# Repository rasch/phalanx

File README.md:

# Phalanx

![The Phalanx Keyboard, Version 0.1.0][image]

The [Phalanx] is a <kbd>4</kbd> <kbd>×</kbd> <kbd>3</kbd> <kbd>+</kbd> <kbd>2</kbd>,
*ortholinear*, *staggered*, *split* keyboard.

- Keyboard Maintainer: [rasch](https://github.com/rasch/phalanx)
- Hardware Supported: Phalanx 0.1.0 (stm32f072)
- Hardware Availability: [phalanx]

## Getting Board

Check out [the Phalanx releases page][releases] for the required files to get
PCBs manufactured (`plot.zip`) and/or assembled (`bom.csv` and `cpl.csv`). For
those with soldering abilities, an interactive BOM/CPL HTML file (`ibom.html`)
is provided to aid with self-assembly.

During development, it may be preferable (faster) to run rule checks and test
builds locally. There is a `run` shell script in the root of this repository
that is used by the CI/CD for building releases. This script can be run
directly (`./run pcb`), but it requires the `kicad-cli` 8.0+ release to be
installed. Instead, if `podman` is available, it is recommended to use the
`build` script. This script just runs the `./run` script in the
`kicad/kicad:8.0` container. The build files and reports (ERC/DRC) are placed in
the `dist` directory.

![The Phalanx Keyboard, Version 0.1.0][image-pcb]

In addition to the parts listed in the BOM, the following will be needed for a
complete keyboard:

- 28 x Kailh Low Profile Choc Switches (PG1350)
- 28 x 1u Choc Keycaps (such as MBK, I prefer the convex keys for the thumbs)
- USB-C cable to connect to device
- RJ45 Ethernet Cable to connect keyboard halves (the monoprice micro slimrun
  patch cable works well, I've used the 6 inch cable)
- Some rubber feet or neoprene adhesive rubber pads to prevent the board from
  sliding all over the place

## Firmware Installation

Download the firmware, `phalanx_default.bin`, from [the Phalanx releases
page][releases]. To flash the keyboard, press the reset button on the PCB to
enter bootloader mode, then run:

```sh
dfu-util -a 0 -d 0483:DF11 -s 0x8000000:leave -D phalanx_default.bin
```

For details on compiling the firmware, please see the [Github Actions
workflow][build].

## Keymap

The base alpha layer is based on the [Engram] layout.

```txt
  B  Y  O  U       L  D  W  V
  C  I  E  A       H  T  S  N
  G  X  J  K       R  M  F  P
            ␣    ⌫
```

[QMK] features such as `Mod-Tap`, `Layers`, `Combos` and `Tap Dance` are
utilized to maximize Phalanx's features with only 27% of the keys from a
standard keyboard. Please visit the [Phalanx website][phalanx] for details of
the layout.

## License

[Solderpad Hardware License v2.1](LICENSE)

[phalanx]: https://www.rasch.co/phalanx
[releases]: https://github.com/rasch/phalanx/releases/
[image]: https://i.imgur.com/y4TYriW.jpg
[image-pcb]: https://i.imgur.com/gtF0UkI.png
[build]: https://github.com/rasch/phalanx/blob/main/.github/workflows/fw.yml
[engram]: https://engram.dev/
[qmk]: https://docs.qmk.fm/#/
[//]: https://en.wikipedia.org/wiki/Phalanx_bone

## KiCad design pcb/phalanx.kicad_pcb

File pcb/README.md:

# Phalanx PCB

![The Phalanx PCB, Version 0.1.0][pcb image]

## Getting Board

Check out [the Phalanx releases page][releases] for the required files to get
PCBs manufactured (`plot.zip`) and/or assembled (`bom.csv` and `cpl.csv`). For
those with soldering abilities, an interactive BOM/CPL HTML file (`ibom.html`)
is provided to aid with self-assembly.

## Build Locally

During development, it may be preferable (faster) to run rule checks and test
builds locally. There is a `run` shell script in the root of this repository
that is used by the CI/CD for building releases. This script can be run
directly (`./run build`), but it requires the `kicad-cli` nightly release to be
installed. Instead, if `podman` is available, it is recommended to use the
`build-pcb` script. This script just runs the `./run` script in the
`kicad/kicad:nightly` container. The build files and reports (ERC/DRC) are
placed in the `dist` directory.

[pcb image]: https://cdn.jsdelivr.net/gh/rasch/phalanx@assets/phalanx-fpcb.webp
[releases]: https://github.com/rasch/phalanx/releases/

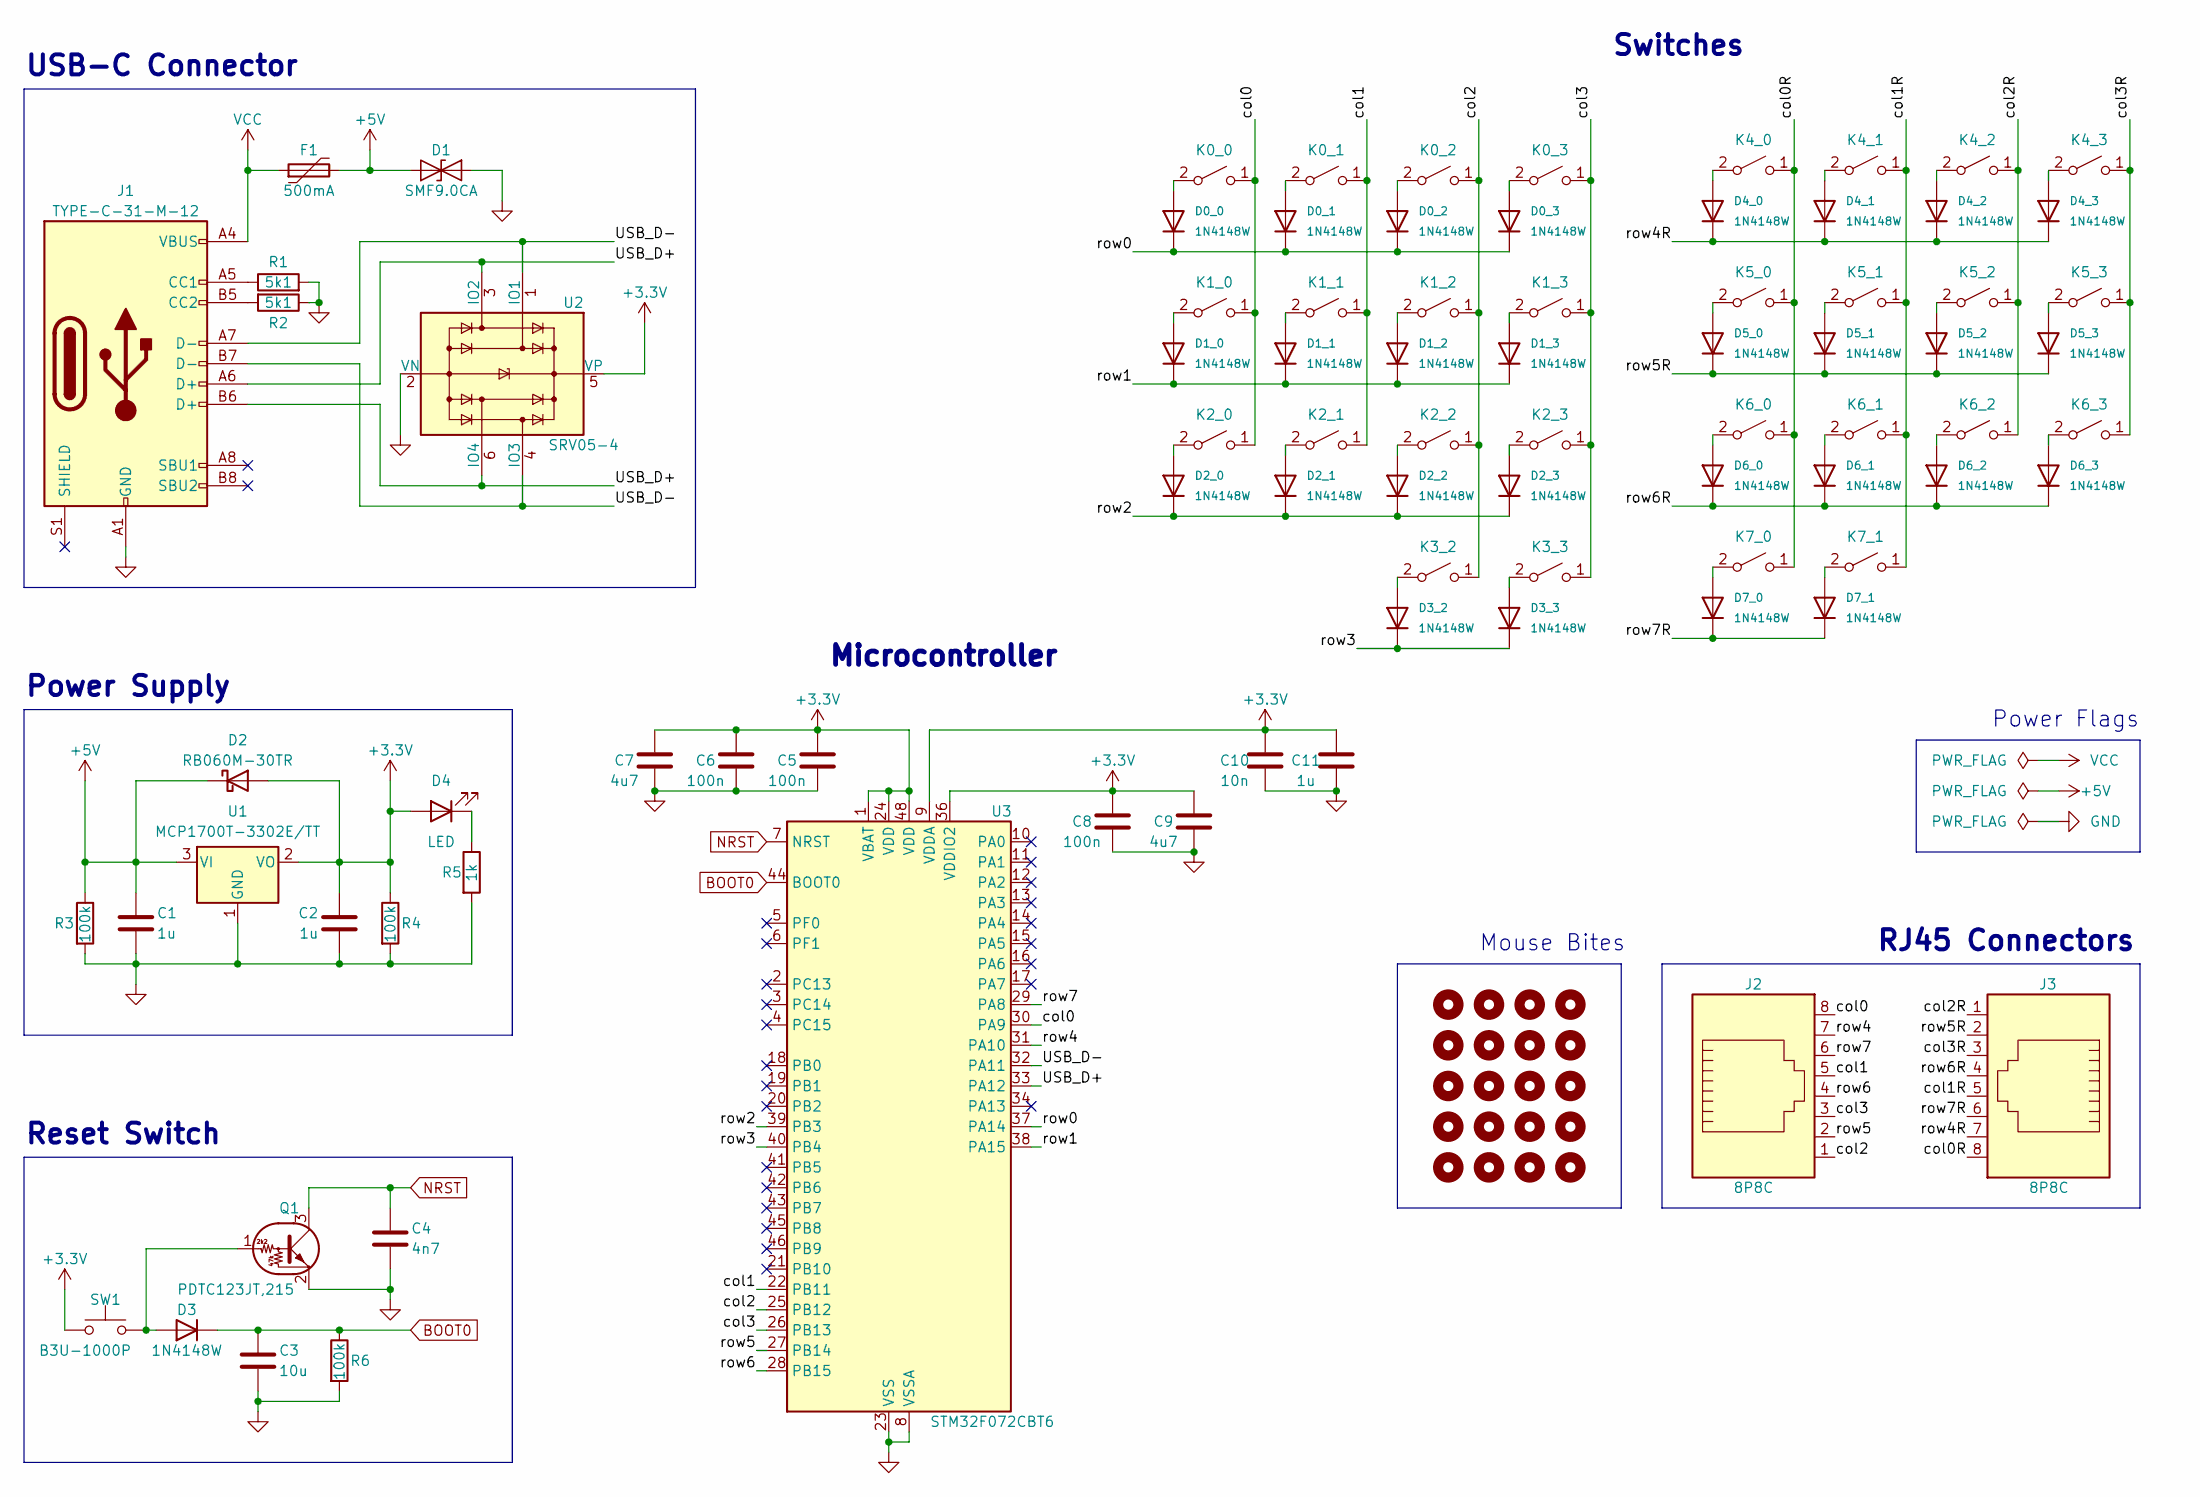
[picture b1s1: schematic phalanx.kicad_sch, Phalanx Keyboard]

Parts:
C1, C2, C11: 1u; C_0805_2012Metric; Part Name Capacitor; LCSC Part C28323
C3: 10u; C_0805_2012Metric; Part Name Capacitor; LCSC Part C17024
C4: 4n7; C_0805_2012Metric; Part Name Capacitor; LCSC Part C717014
C5, C6, C8: 100n; C_0805_2012Metric; Part Name Capacitor; LCSC Part C49678
C7, C9: 4u7; C_0805_2012Metric; Part Name Capacitor; LCSC Part C87998
C10: 10n; C_0805_2012Metric; Part Name Capacitor; LCSC Part C1710
D0_0, D0_1, D0_2, D0_3, D1_0, D1_1, D1_2, D1_3, D2_0, D2_1, D2_2, D2_3, D3, D3_2, D3_3, D4_0, D4_1, D4_2, D4_3, D5_0, D5_1, D5_2, D5_3, D6_0, D6_1, D6_2, D6_3, D7_0, D7_1: 1N4148W; D_SOD-123; Part Name Diode; LCSC Part C81598
D1: SMF9.0CA; D_SOD-123; Part Name Bidirectional Diode; LCSC Part C435473
D2: RB060M-30TR; D_SOD-123; Part Name Schottky Barrier Diodes; LCSC Part C559324
D4: LED; LED_0603_1608Metric; Part Name Red LED; LCSC Part C84263
F1: 500mA; Fuse_1206_3216Metric; Part Name Polyfuse; LCSC Part C151162
H1, H2, H3, H4, H5, H6, H7, H8, H9, H10, H11, H12, H13, H14, H15, H16, H17, H18, H19, H20: MountingHole; MountingHole_0.5mm
J1: TYPE-C-31-M-12; USB_C_Receptacle_HRO_TYPE-C-31-M-12; Part Name USB C; LCSC Part C165948
J2, J3: 8P8C; RJ45; Part Name RJ45 Receptacle; LCSC Part C2902700
K0_0, K0_1, K0_2, K0_3, K1_0, K1_1, K1_2, K1_3, K2_0, K2_1, K2_2, K2_3, K3_2, K3_3, K4_0, K4_1, K4_2, K4_3, K5_0, K5_1, K5_2, K5_3, K6_0, K6_1, K6_2, K6_3, K7_0, K7_1: SW_KEY; Choc_PG1350_Choc_Spacing
Q1: PDTC123JT,215; SOT-23; Part Name NPN Transistor; LCSC Part C406040
R1, R2: 5k1; R_0805_2012Metric; Part Name Resistor; LCSC Part C27834
R3, R4, R6: 100k; R_0805_2012Metric; Part Name Resistor; LCSC Part C149504
R5: 1k; R_0805_2012Metric; Part Name Resistor; LCSC Part C17513
SW1: B3U-1000P; SW_SPST_B3U-1000P; Part Name Reset Button; LCSC Part C231329
U1: MCP1700T-3302E/TT; SOT-23; Part Name Dropout Regulator; LCSC Part C39051
U2: SRV05-4; SOT-23-6; Part Name TVS Diode Array; LCSC Part C558418
U3: STM32F072CBT6; LQFP-48_7x7mm_P0.5mm; Part Name MCU; LCSC Part C81720

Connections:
+3.3V: C2.1, C5.1, C6.2, C7.1, C8.2, C9.2, C10.2, C11.2, D2.2 (A), D4.2 (A), R4.1, SW1.1, U1.2 (VO), U2.5 (VP), U3.1 (VBAT), U3.9 (VDDA), U3.24 (VDD), U3.36 (VDDIO2), U3.48 (VDD)
+5V: C1.1, D1.1 (A1), D2.1 (K), F1.2, R3.1, U1.3 (VI)
/USB_D+: J1.A6 (D+), J1.B6 (D+), U2.3 (IO2), U2.6 (IO4), U3.33 (PA12)
/USB_D-: J1.A7 (D-), J1.B7 (D-), U2.1 (IO1), U2.4 (IO3), U3.32 (PA11)
/col0: J2.8, K0_0.1 (A), K1_0.1 (A), K2_0.1 (A), U3.30 (PA9)
/col0R: J3.8, K4_0.1 (A), K5_0.1 (A), K6_0.1 (A), K7_0.1 (A)
/col1: J2.5, K0_1.1 (A), K1_1.1 (A), K2_1.1 (A), U3.22 (PB11)
/col1R: J3.5, K4_1.1 (A), K5_1.1 (A), K6_1.1 (A), K7_1.1 (A)
/col2: J2.1, K0_2.1 (A), K1_2.1 (A), K2_2.1 (A), K3_2.1 (A), U3.25 (PB12)
/col2R: J3.1, K4_2.1 (A), K5_2.1 (A), K6_2.1 (A)
/col3: J2.3, K0_3.1 (A), K1_3.1 (A), K2_3.1 (A), K3_3.1 (A), U3.26 (PB13)
/col3R: J3.3, K4_3.1 (A), K5_3.1 (A), K6_3.1 (A)
/row0: D0_0.1 (K), D0_1.1 (K), D0_2.1 (K), D0_3.1 (K), U3.37 (PA14)
/row1: D1_0.1 (K), D1_1.1 (K), D1_2.1 (K), D1_3.1 (K), U3.38 (PA15)
/row2: D2_0.1 (K), D2_1.1 (K), D2_2.1 (K), D2_3.1 (K), U3.39 (PB3)
/row3: D3_2.1 (K), D3_3.1 (K), U3.40 (PB4)
/row4: J2.7, U3.31 (PA10)
/row4R: D4_0.1 (K), D4_1.1 (K), D4_2.1 (K), D4_3.1 (K), J3.7
/row5: J2.2, U3.27 (PB14)
/row5R: D5_0.1 (K), D5_1.1 (K), D5_2.1 (K), D5_3.1 (K), J3.2
/row6: J2.4, U3.28 (PB15)
/row6R: D6_0.1 (K), D6_1.1 (K), D6_2.1 (K), D6_3.1 (K), J3.4
/row7: J2.6, U3.29 (PA8)
/row7R: D7_0.1 (K), D7_1.1 (K), J3.6
BOOT0: C3.2, D3.1 (K), R6.1, U3.44 (BOOT0)
GND: C1.2, C2.2, C3.1, C4.2, C5.2, C6.1, C7.2, C8.1, C9.1, C10.1, C11.1, D1.2 (A2), J1.A1 (GND), J1.A12 (GND), J1.B1 (GND), J1.B12 (GND), Q1.2 (E), R1.2, R2.1, R3.2, R4.2, R5.2, R6.2, U1.1 (GND), U2.2 (VN), U3.8 (VSSA), U3.23 (VSS), U3.35 (VSS), U3.47 (VSS)
NRST: C4.1, Q1.3 (C), U3.7 (NRST)
unnamed: D0_0.2 (A), K0_0.2 (B)
unnamed: D0_1.2 (A), K0_1.2 (B)
unnamed: D0_2.2 (A), K0_2.2 (B)
unnamed: D0_3.2 (A), K0_3.2 (B)
unnamed: D1_0.2 (A), K1_0.2 (B)
unnamed: D1_1.2 (A), K1_1.2 (B)
unnamed: D1_2.2 (A), K1_2.2 (B)
unnamed: D1_3.2 (A), K1_3.2 (B)
unnamed: D2_0.2 (A), K2_0.2 (B)
unnamed: D2_1.2 (A), K2_1.2 (B)
unnamed: D2_2.2 (A), K2_2.2 (B)
unnamed: D2_3.2 (A), K2_3.2 (B)
unnamed: D3.2 (A), Q1.1 (B), SW1.2
unnamed: D3_2.2 (A), K3_2.2 (B)
unnamed: D3_3.2 (A), K3_3.2 (B)
unnamed: D4.1 (K), R5.1
unnamed: D4_0.2 (A), K4_0.2 (B)
unnamed: D4_1.2 (A), K4_1.2 (B)
unnamed: D4_2.2 (A), K4_2.2 (B)
unnamed: D4_3.2 (A), K4_3.2 (B)
unnamed: D5_0.2 (A), K5_0.2 (B)
unnamed: D5_1.2 (A), K5_1.2 (B)
unnamed: D5_2.2 (A), K5_2.2 (B)
unnamed: D5_3.2 (A), K5_3.2 (B)
unnamed: D6_0.2 (A), K6_0.2 (B)
unnamed: D6_1.2 (A), K6_1.2 (B)
unnamed: D6_2.2 (A), K6_2.2 (B)
unnamed: D6_3.2 (A), K6_3.2 (B)
unnamed: D7_0.2 (A), K7_0.2 (B)
unnamed: D7_1.2 (A), K7_1.2 (B)
unnamed: J1.A5 (CC1), R1.1
unnamed: J1.B5 (CC2), R2.2
VCC: F1.1, J1.A4 (VBUS), J1.A9 (VBUS), J1.B4 (VBUS), J1.B9 (VBUS)

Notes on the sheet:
Power Flags
Switches
USB-C Connector
Power Supply
Microcontroller
Reset Switch
RJ45 Connectors
Mouse Bites

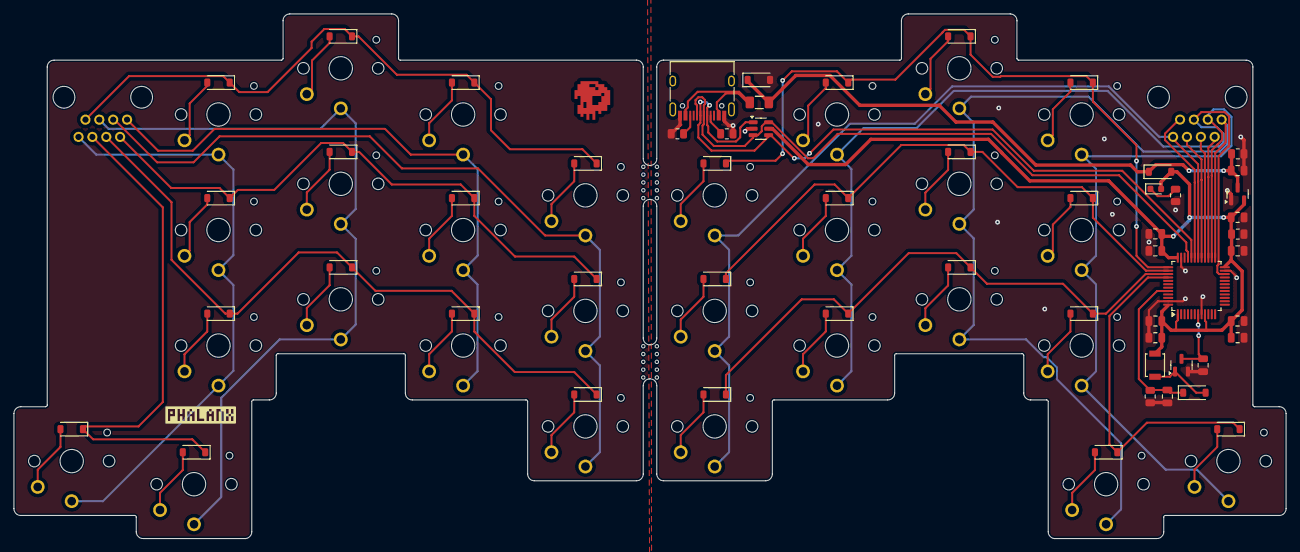
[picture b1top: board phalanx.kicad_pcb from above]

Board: 2 copper layers, 187.2 x 77.2 mm, 106 parts (0 on the bottom side), 60 nets.

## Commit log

2023-11-22 🎉 Initial commit
2023-11-29 ✨ Add PCB files and LICENSE
2023-11-29 🍱 Add PCB front image
2023-11-30 🚨 Fix DRC (design rule check) warnings
2023-12-01 🚸 Add LCSC Part numbers to schematic symbols
2023-12-01 🚚 Rename a couple files
2023-12-01 👷 Add script to generate manufacturing files
2023-12-02 👷 Configure release automation
2023-12-02 📝 Add documentation for PCB releases
2024-03-09 ✨ Add firmware configuration
2024-03-09 ✨ Add updated PCB files
2024-03-09 🐛 Increase resistance on pwr LED
2024-03-11 ✨ Add firmware for 18-key option
    Just to try out Ben Vallack's Piano layout
2024-03-11 📚 Update documentation (WIP)
2024-03-18 📚 Start keymap documentation
2024-06-16 📝 Add documentation website with keymap
2024-06-16 📝 Add note about required parts
2024-06-17 📝 Add addional keymap documentation
2024-06-17 🚨 Fix qmk compiler warnings
    Migrate qmk keyboard firmware from info.json to keyboard.json and remove
    empty rules.mk file.
2024-06-17 👷 Switch to kicad stable for CI/build
    The erc and drc reporting is now available in the stable (8.0) version
    of the kicad-cli!
2024-06-17 💚 Fix CI/build
    Update files from KiCad 7 to KiCad 8 and fix all DRC/ERC errors.
2024-06-17 💚 Fix CI for firmware compilation
2024-06-17 💚 Fix release notes
2026-05-03 📚 Update link to engram layout documentation
    The old link now belongs to an online casino.
